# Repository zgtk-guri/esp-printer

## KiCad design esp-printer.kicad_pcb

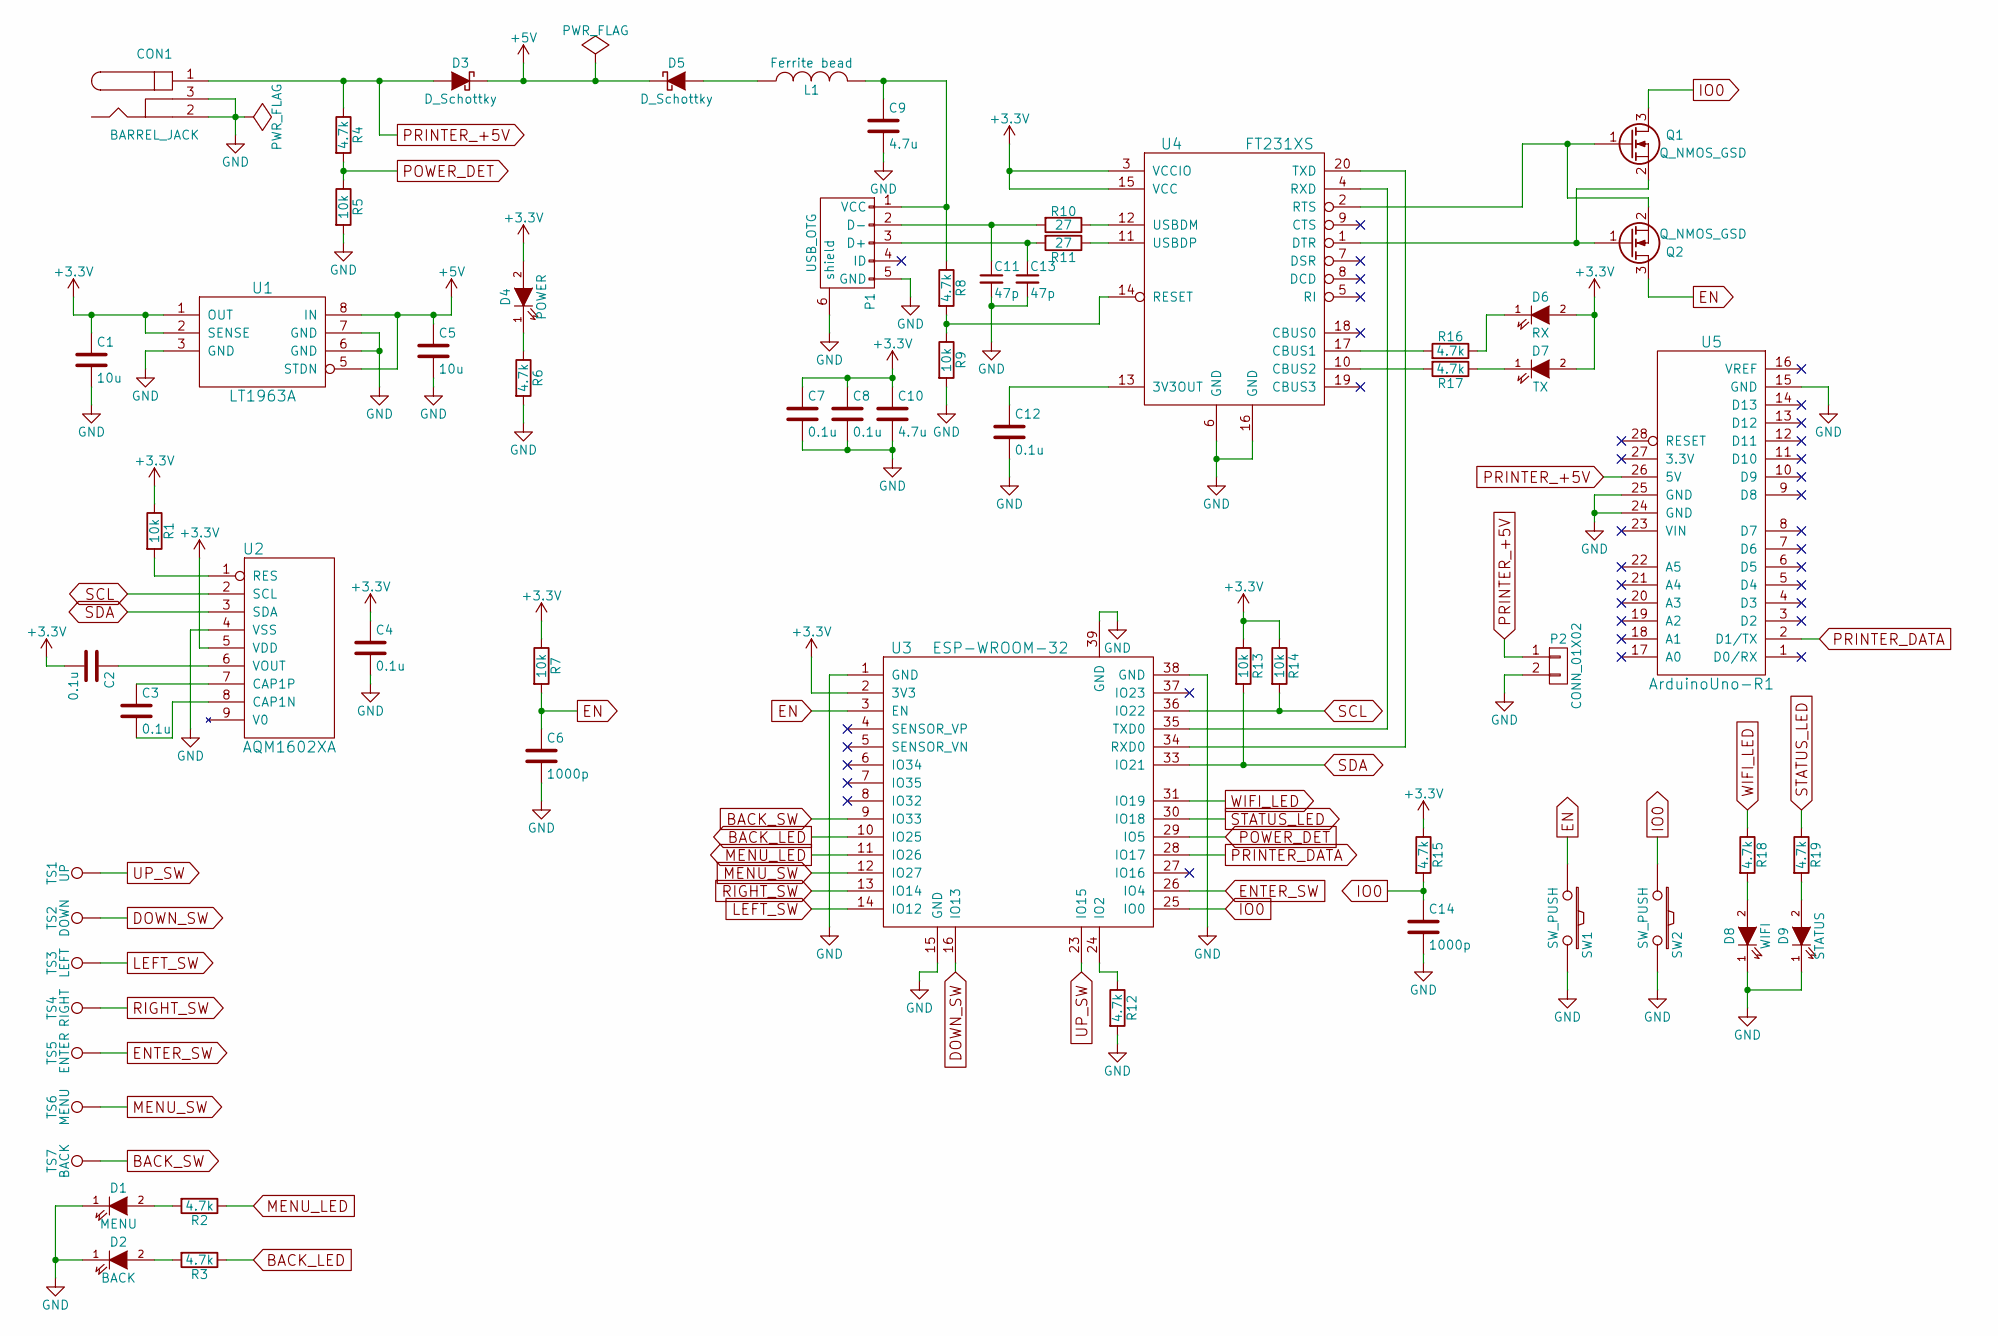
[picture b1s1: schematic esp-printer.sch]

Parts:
C1, C5: 10u; C_0805_HandSoldering
C2, C3, C4, C7, C8, C12: 0.1u; C_0603_HandSoldering
C6, C14: 1000p; C_0603_HandSoldering
C9, C10: 4.7u; C_0603_HandSoldering
C11, C13: 47p; C_0603_HandSoldering
CON1: BARREL_JACK; MJ-179PH
D1: MENU; LED-0603
D2: BACK; LED-0603
D3, D5: D_Schottky; SOD-123
D4: POWER; LED-0603
D6: RX; LED-0603
D7: TX; LED-0603
D8: WIFI; LED-0603
D9: STATUS; LED-0603
L1: Ferrite bead; R_0805_HandSoldering
P1: USB_OTG; ZX62R-B-5P
P2: CONN_01X02; B2P-VH
Q1, Q2: Q_NMOS_GSD; SOT-23_Handsoldering
R1, R5, R7, R9, R13, R14: 10k; R_0603_HandSoldering
R2, R3, R4, R6, R8, R12, R15, R16, R17, R18, R19: 4.7k; R_0603_HandSoldering
R10, R11: 27; R_0603_HandSoldering
SW1, SW2: SW_PUSH; SKRPACE010
TS1: UP; TouchPad_Arrow
TS2: DOWN; TouchPad_Arrow
TS3: LEFT; TouchPad_Arrow
TS4: RIGHT; TouchPad_Arrow
TS5: ENTER; TouchPad_Square
TS6: MENU; TouchPad_Square
TS7: BACK; TouchPad_Square
U1: LT1963A; SOIC-8-N
U2: AQM1602XA
U3: ESP-WROOM-32
U4: FT231XS; SSOP-20
U5: ArduinoUno-R1

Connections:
+3V3: C1.1, C2.2, C4.1, C7.1, C8.1, C10.1, D4.2 (A), D6.2 (A), D7.2 (A), R1.1, R7.1, R13.1, R14.1, R15.1, U1.1 (OUT), U1.2 (SENSE), U2.5 (VDD), U3.2 (3V3), U4.3 (VCCIO), U4.15 (VCC)
+5V: C5.1, D3.1 (K), D5.1 (K), U1.5 (STDN), U1.8 (IN)
BACK_LED: R3.1, U3.10 (IO25)
BACK_SW: TS7.1, U3.9 (IO33)
DOWN_SW: TS2.1, U3.16 (IO13)
EN: C6.1, Q2.3 (D), R7.2, SW1.1, U3.3 (EN)
ENTER_SW: TS5.1, U3.26 (IO4)
GND: C1.2, C4.2, C5.2, C6.2, C7.2, C8.2, C9.2, C10.2, C11.2, C12.2, C13.2, C14.2, CON1.2, CON1.3, D1.1 (K), D2.1 (K), D8.1 (K), D9.1 (K), P1.5 (GND), P1.6 (shield), P2.2, R5.2, R6.2, R9.2, R12.2, SW1.2, SW2.2, U1.3 (GND), U1.6 (GND), U1.7 (GND), U2.4 (VSS), U3.1 (GND), U3.15 (GND), U3.38 (GND), U3.39 (GND), U4.6 (GND), U4.16 (GND), U5.15 (GND), U5.24 (GND), U5.25 (GND)
IO0: C14.1, Q1.3 (D), R15.2, SW2.1, U3.25 (IO0)
LEFT_SW: TS3.1, U3.14 (IO12)
MENU_LED: R2.1, U3.11 (IO26)
MENU_SW: TS6.1, U3.12 (IO27)
unnamed: C2.1, U2.6 (VOUT)
unnamed: C3.1, U2.7 (CAP1P)
unnamed: C3.2, U2.8 (CAP1N)
unnamed: C9.1, L1.2, P1.1 (VCC), R8.1
unnamed: C11.1, P1.2 (D-), R10.2
unnamed: C12.1, U4.13 (3V3OUT)
unnamed: C13.1, P1.3 (D+), R11.2
unnamed: D1.2 (A), R2.2
unnamed: D2.2 (A), R3.2
unnamed: D4.1 (K), R6.1
unnamed: D5.2 (A), L1.1
unnamed: D6.1 (K), R16.1
unnamed: D7.1 (K), R17.1
unnamed: D8.2 (A), R18.2
unnamed: D9.2 (A), R19.2
unnamed: Q1.1 (G), Q2.2 (S), U4.2 (RTS)
unnamed: Q1.2 (S), Q2.1 (G), U4.1 (DTR)
unnamed: R1.2, U2.1 (RES)
unnamed: R8.2, R9.1, U4.14 (RESET)
unnamed: R10.1, U4.12 (USBDM)
unnamed: R11.1, U4.11 (USBDP)
unnamed: R12.1, U3.24 (IO2)
unnamed: R16.2, U4.17 (CBUS1)
unnamed: R17.2, U4.10 (CBUS2)
unnamed: U3.34 (RXD0), U4.20 (TXD)
unnamed: U3.35 (TXD0), U4.4 (RXD)
POWER_DET: R4.2, R5.1, U3.29 (IO5)
PRINTER_+5V: CON1.1, D3.2 (A), P2.1, R4.1, U5.26 (5V)
PRINTER_DATA: U3.28 (IO17), U5.2 (D1/TX)
RIGHT_SW: TS4.1, U3.13 (IO14)
SCL: R14.2, U2.2 (SCL), U3.36 (IO22)
SDA: R13.2, U2.3 (SDA), U3.33 (IO21)
STATUS_LED: R19.1, U3.30 (IO18)
UP_SW: TS1.1, U3.23 (IO15)
WIFI_LED: R18.1, U3.31 (IO19)

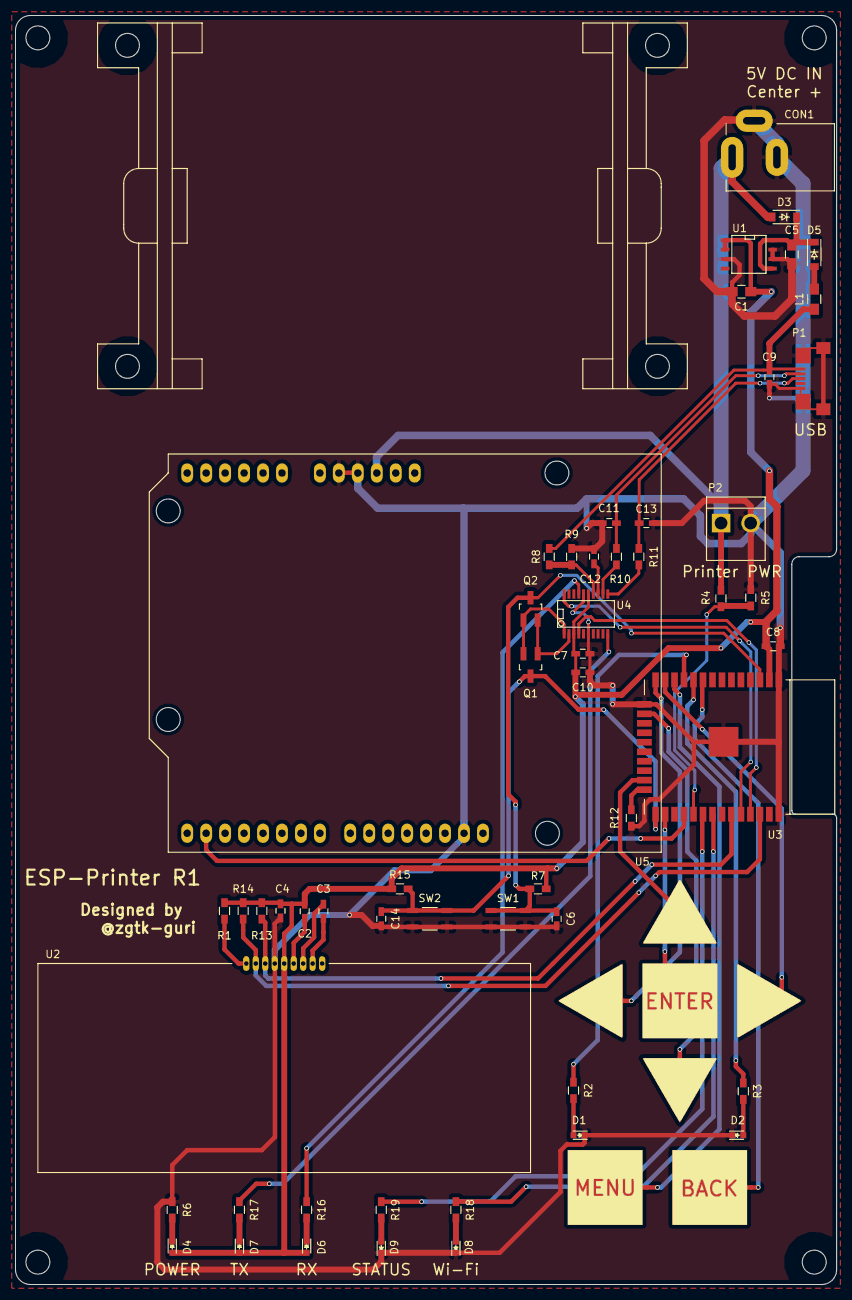
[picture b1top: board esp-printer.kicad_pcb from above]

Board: 2 copper layers, 110.0 x 170.0 mm, 62 parts (0 on the bottom side), 47 nets.

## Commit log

2017-08-08 init repo and create a kicad project
2017-08-17 Add a schematic
2017-08-18 Assign footprints with cvpcb
2017-09-14 Add a PCB pattern
2017-09-18 Output gerber files for manufacturing
2017-09-18 Move hardware design files to a new folder
